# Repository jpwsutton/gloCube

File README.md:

gloCube
=======

Glowing Notification Moodlamp Code

This project consists of a number of python scripts and an Arduino .ino
sketch. Some or all of which might be of use to members of the community that wish
to build similar notification projects.

The related blog post: http://www.jsutton.co.uk/wordpress/?p=190

The wiki page: http://wiki.jsutton.co.uk/doku.php?id=projects:glocube

gloCube.ino
-----------
This Arduino sketch is written for the Teensy++ 2.0 but can be adapted to be
run on a normal Arduino.

It makes use of the SerialCommand Library, which can be found here: https://github.com/scogswell/ArduinoSerialCommand

Once it has been uploaded, useage is as follows:

To use the running code, connect to the serial port and send one of two commands.

```F <LED ID> <R value> <G value> <B value>```

 – This will fade the selected LED to the specified colour e.g. ```F 0 255 0 0``` will fade LED 0 to red.

```L <Flash No.> <R value> <G value> <B value>```

 – This will flash all LEDs N number of times at the specified colour e.g. ```L 5 0 255 0``` Will flash all LEDs five times green.

To do
-----
- [x] Convert python/gmail_checker.pl to python (And maybe get rid of the curl command).
- [ ] Separate out some of the logic so that the cube control is done from a module.
- [ ] Make it work on windows.
- [x] Make it deal with a dropped or missing serial port.
- [x] Find a better solution than the current subprocesses. (facebook login is still launched via a sub process)

Author
------

James Sutton - Original sketch and python scripts

Thanks
------

* Thanks to Steven Cogswell for the SerialCommand Library used in the Firmware for the Cube -  https://github.com/scogswell/ArduinoSerialCommand
* Thanks to pcardune for the Facebook login script - http://blog.carduner.net/2010/05/26/authenticating-with-facebook-on-the-command-line-using-python/

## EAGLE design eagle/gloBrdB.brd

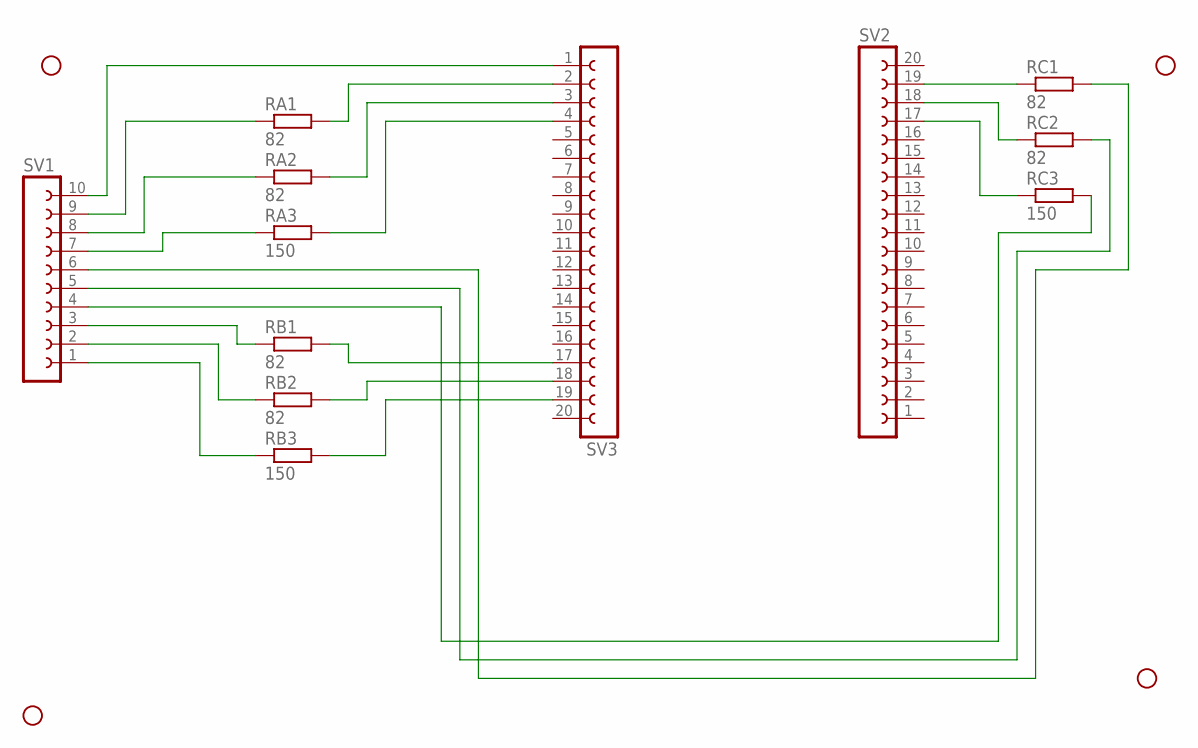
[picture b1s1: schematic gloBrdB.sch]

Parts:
RA1, RA2: 82; 0204/7
RA3: 150; 0204/7
RB1, RB2: 82; 0204/7
RB3: 150; 0204/7
RC1, RC2: 82; 0204/7
RC3: 150; 0204/7
STANDOFF1, STANDOFF2, STANDOFF3, STANDOFF4: STAND-OFF
SV1: FE10-1; FE10
SV2, SV3: FE20-1; FE20

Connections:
unnamed: SV1.10, SV3.1
unnamed: RA1.2, SV3.2
unnamed: RA2.2, SV3.3
unnamed: RA3.2, SV3.4
unnamed: RB3.2, SV3.19
unnamed: RB2.2, SV3.18
unnamed: RB1.2, SV3.17
unnamed: RC3.2, SV1.4
unnamed: RC2.2, SV1.5
unnamed: RC1.2, SV1.6
unnamed: RC1.1, SV2.19
unnamed: RC2.1, SV2.18
unnamed: RC3.1, SV2.17
unnamed: RA1.1, SV1.9
unnamed: RA2.1, SV1.8
unnamed: RA3.1, SV1.7
unnamed: RB1.1, SV1.3
unnamed: RB2.1, SV1.2
unnamed: RB3.1, SV1.1

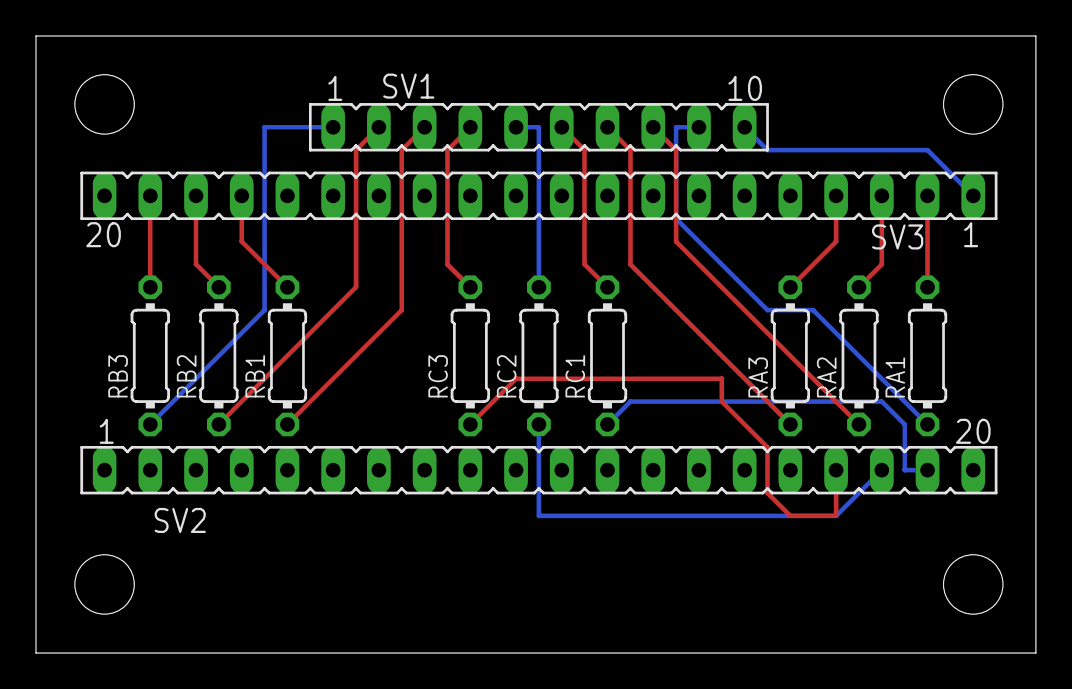
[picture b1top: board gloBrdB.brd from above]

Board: 2 copper layers, 55.5 x 34.3 mm, 16 parts (0 on the bottom side), 19 nets.

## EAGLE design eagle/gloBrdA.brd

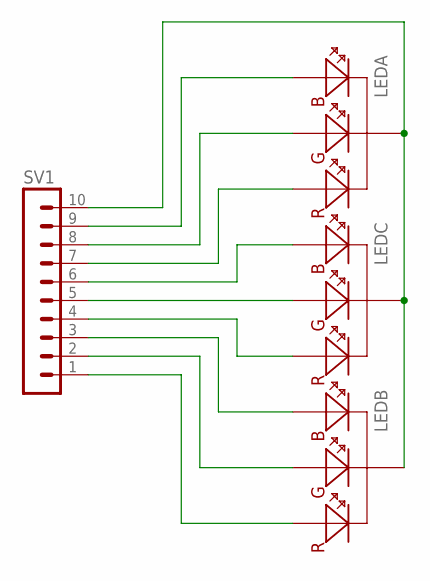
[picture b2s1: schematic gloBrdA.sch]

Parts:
LEDA: MULTICOLORLED
LEDB: MULTICOLORLED
LEDC: MULTICOLORLED
SV1: MA10-1

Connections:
GND: LEDA.GND, LEDB.GND, LEDC.GND, SV1.10
unnamed: LEDC.LED-G, SV1.5
unnamed: LEDA.LED-B, SV1.9
unnamed: LEDA.LED-G, SV1.8
unnamed: LEDA.LED-R, SV1.7
unnamed: LEDC.LED-B, SV1.6
unnamed: LEDC.LED-R, SV1.4
unnamed: LEDB.LED-B, SV1.3
unnamed: LEDB.LED-G, SV1.2
unnamed: LEDB.LED-R, SV1.1

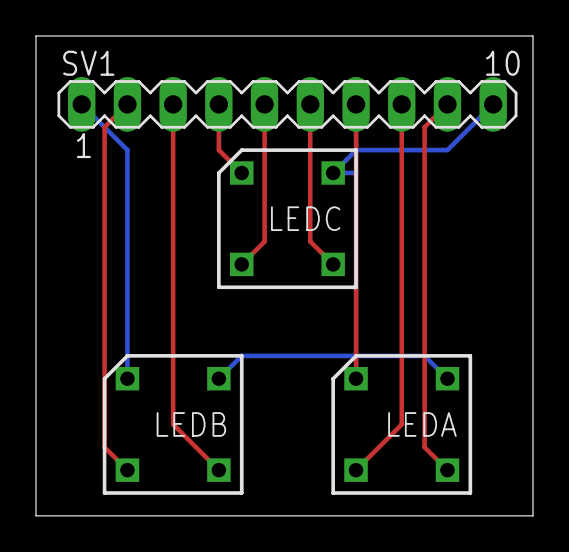
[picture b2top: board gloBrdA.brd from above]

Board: 2 copper layers, 27.6 x 26.7 mm, 4 parts (0 on the bottom side), 10 nets.

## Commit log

2013-04-07 Initial commit of gloCube.ino firmware for teensy++
2013-04-07 Ran all python files though autopep8 and added .gitignore
2013-04-07 Added To Do to the Readme
2013-04-07 Initial Commit of python and perl scripts
2013-04-07 Added subprocess todo item
2013-04-07 Added thanks to pcardune
2013-04-10 Consolidated facebook and gmail checkers into the connector script
2013-04-10 Removing facebook and gmail scripts
2013-04-11 Updated todo list in README.md
2013-04-12 Fixing gmail check in glowConnector.py
2013-04-12 Adding config code to facebook_login.py
2013-04-21 Adding Eagle schematics and boards

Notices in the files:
parts and their libraries:
SparkFun-Electromechanical: Licensing: CC v3.0 Share-Alike You are welcome to use this library for commercial purposes.
